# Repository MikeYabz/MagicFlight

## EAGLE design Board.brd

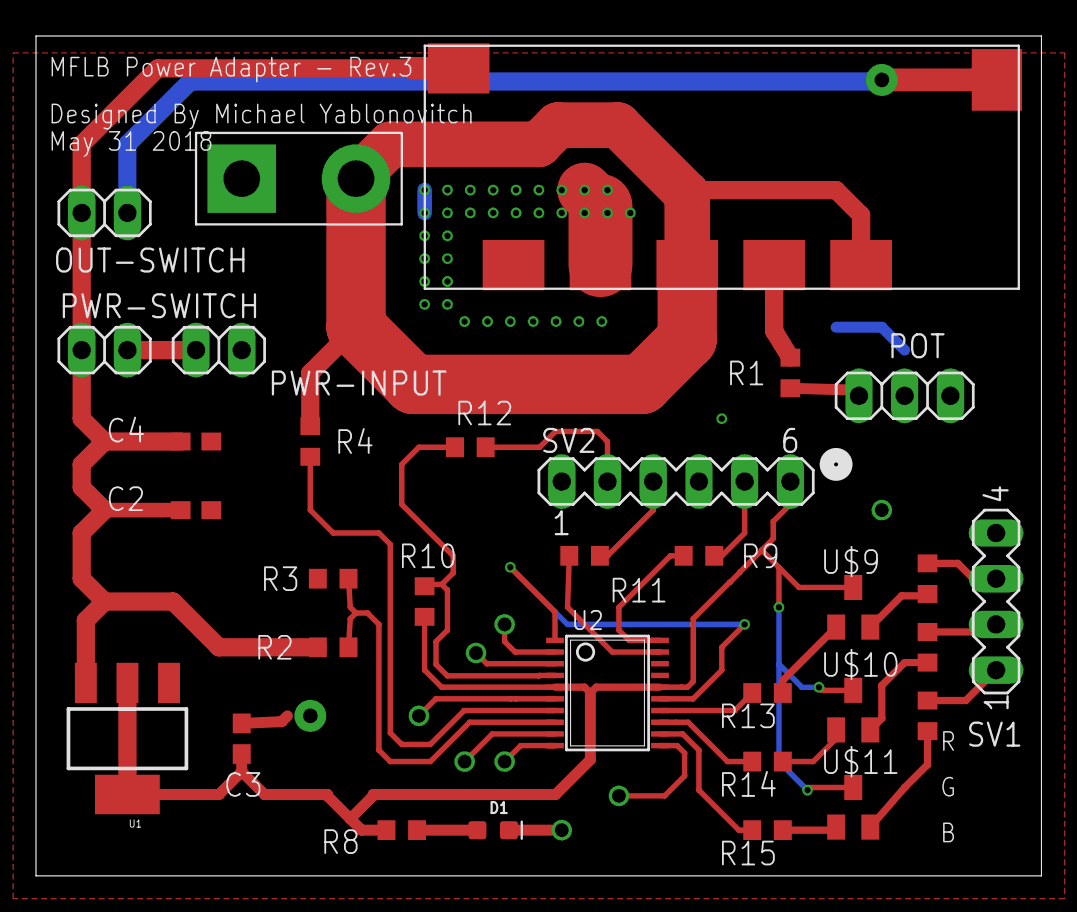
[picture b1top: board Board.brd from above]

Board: 2 copper layers, 55.9 x 46.7 mm, 32 parts (0 on the bottom side), 29 nets.

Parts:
C2: 47uF; C0603
C3: 10uF; C0603
C4: 22uF; C0603
D1: BLUE; LED-0603
OKY-T/16-D12N-C: OKY-T/16-D12N-C
OUT-SWITCH: 1X02
POT: 100k; 1X03
POWER: POWER
PWR-INPUT: 1X02
PWR-SWITCH: 1X02
R1: 9.1k; R0603
R2: 7.5k; R0603
R3: 2.5k; R0603
R4: 1k; R0603
R5, R13, R14, R15: 250; R0603
R6, R7: 200; R0603
R8: 180r; R0603
R9, R11, R12: 250r; R0603
R10: 3k3; R0603
SV1: MA04-1
SV2: MA06-1
U1: SOT223
U2: STM32F07; TSSOP20
U$9, U$10, U$11: P-MOS-FET; SOT23

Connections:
+3V3: C3.1, R8.2, R10.1, SV2.6, U1.2, U1.4, U2.5, U2.16, U$9.E, U$10.E, U$11.E
GND: C2.2, C3.2, C4.2, D1.C, OKY-T/16-D12N-C.PIN4, POT.2, POWER.GND, PWR-INPUT.1, R3.1, SV1.4, SV2.4, U1.1, U2.1, U2.15
LED-B: R15.2, U2.12
LED-G: R14.2, U2.13
LED-R: R13.2, U2.14
unnamed: OKY-T/16-D12N-C.PIN1, OUT-SWITCH.2
unnamed: R5.2, SV1.3
unnamed: POT.1, R1.1
unnamed: OKY-T/16-D12N-C.PIN6, R1.2
unnamed: R6.2, SV1.2
unnamed: R7.2, SV1.1
unnamed: R13.1, U$9.B
unnamed: R14.1, U$10.B
unnamed: R4.2, U2.7
unnamed: D1.A, R8.1
unnamed: R15.1, U$11.B
unnamed: R5.1, U$9.C
unnamed: R6.1, U$10.C
unnamed: R2.2, R3.2, U2.8
unnamed: R7.1, U$11.C
unnamed: R9.2, SV2.5
unnamed: R11.2, SV2.3
unnamed: R12.2, SV2.2
NRST: R10.2, R12.1, U2.4
SWCLK: R9.1, U2.20
SWDIO: R11.1, U2.19
VBAT: PWR-INPUT.2, PWR-SWITCH.2
VIN: C2.1, C4.1, OKY-T/16-D12N-C.PIN2, OUT-SWITCH.1, PWR-SWITCH.1, R2.1, U1.3
VOUT: OKY-T/16-D12N-C.PIN5, OKY-T/16-D12N-C.PIN7, POWER.VOUT, R4.1

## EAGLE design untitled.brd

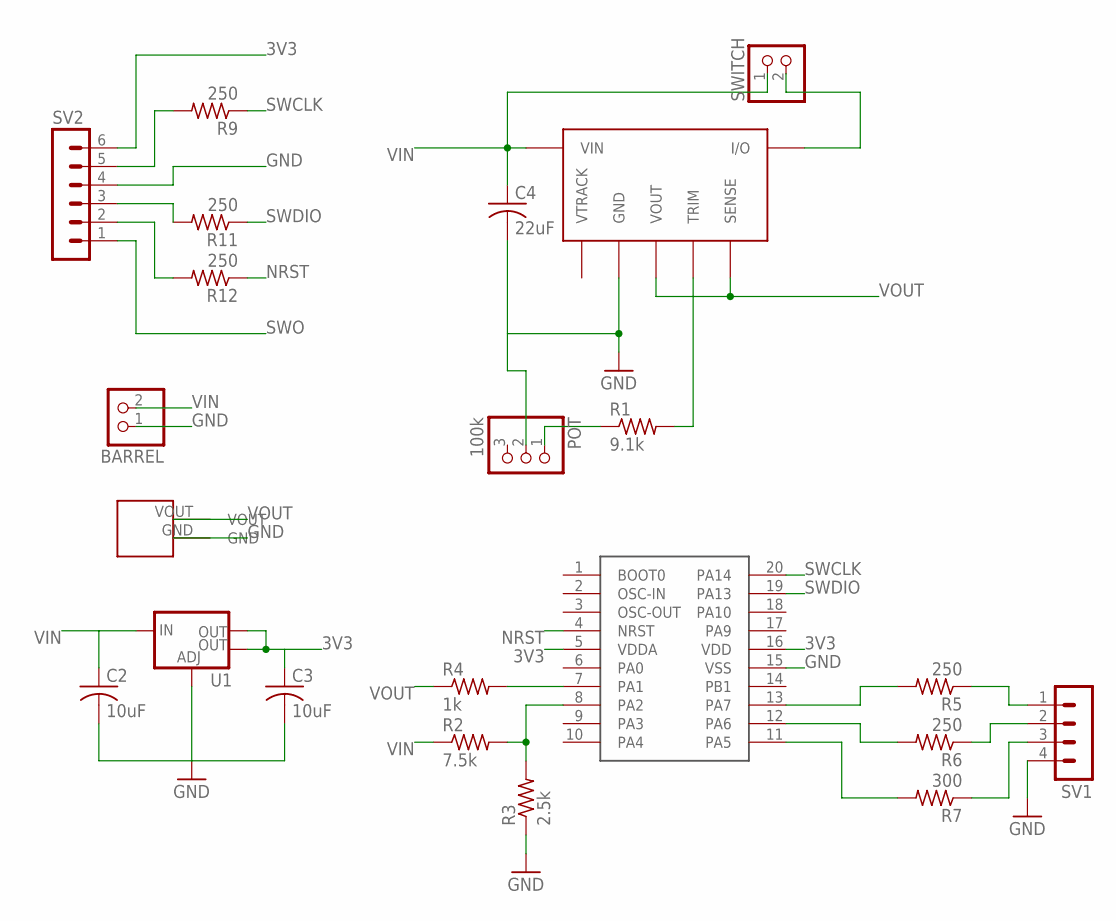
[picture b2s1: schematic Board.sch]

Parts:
BARREL: PINHD-1X2; 1X02
C2, C3: 10uF; C0805
C4: 22uF; C0805
OKY-T/16-D12N-C: OKY-T/16-D12N-C
POT: 100k; 1X03
POWER: POWER
R1: 9.1k; R0805
R2: 7.5k; R0805
R3: 2.5k; R0805
R4: 1k; R0805
R5, R6, R9, R11, R12: 250; R0805
R7: 300; R0805
SV1: MA04-1
SV2: MA06-1
SWITCH: PINHD-1X2; 1X02
U1: V_REG_LM1117SOT223; SOT223
U$1: STM32F07; TSSOP20

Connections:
3V3: C3.1, SV2.6, U1.2 (OUT), U1.4 (OUT), U$1.5 (VDDA), U$1.16 (VDD)
GND: BARREL.1, C2.2, C3.2, C4.2, OKY-T/16-D12N-C.PIN4 (GND), POT.2, POWER.GND, R3.1, SV1.4, SV2.4, U1.1 (ADJ), U$1.15 (VSS)
unnamed: OKY-T/16-D12N-C.PIN1 (I/O), SWITCH.2
unnamed: R5.1, SV1.1
unnamed: POT.1, R1.1
unnamed: OKY-T/16-D12N-C.PIN6 (TRIM), R1.2
unnamed: R2.2, R3.2, U$1.8 (PA2)
unnamed: R7.2, U$1.11 (PA5)
unnamed: R5.2, U$1.13 (PA7)
unnamed: R6.2, U$1.12 (PA6)
unnamed: R4.2, U$1.7 (PA1)
unnamed: R6.1, SV1.2
unnamed: R7.1, SV1.3
unnamed: R9.2, SV2.5
unnamed: R11.2, SV2.3
unnamed: R12.2, SV2.2
NRST: R12.1, U$1.4 (NRST)
SWCLK: R9.1, U$1.20 (PA14)
SWDIO: R11.1, U$1.19 (PA13)
SWO: SV2.1
VIN: BARREL.2, C2.1, C4.1, OKY-T/16-D12N-C.PIN2 (VIN), R2.1, SWITCH.1, U1.3 (IN)
VOUT: OKY-T/16-D12N-C.PIN5 (VOUT), OKY-T/16-D12N-C.PIN7 (SENSE), POWER.VOUT, R4.1

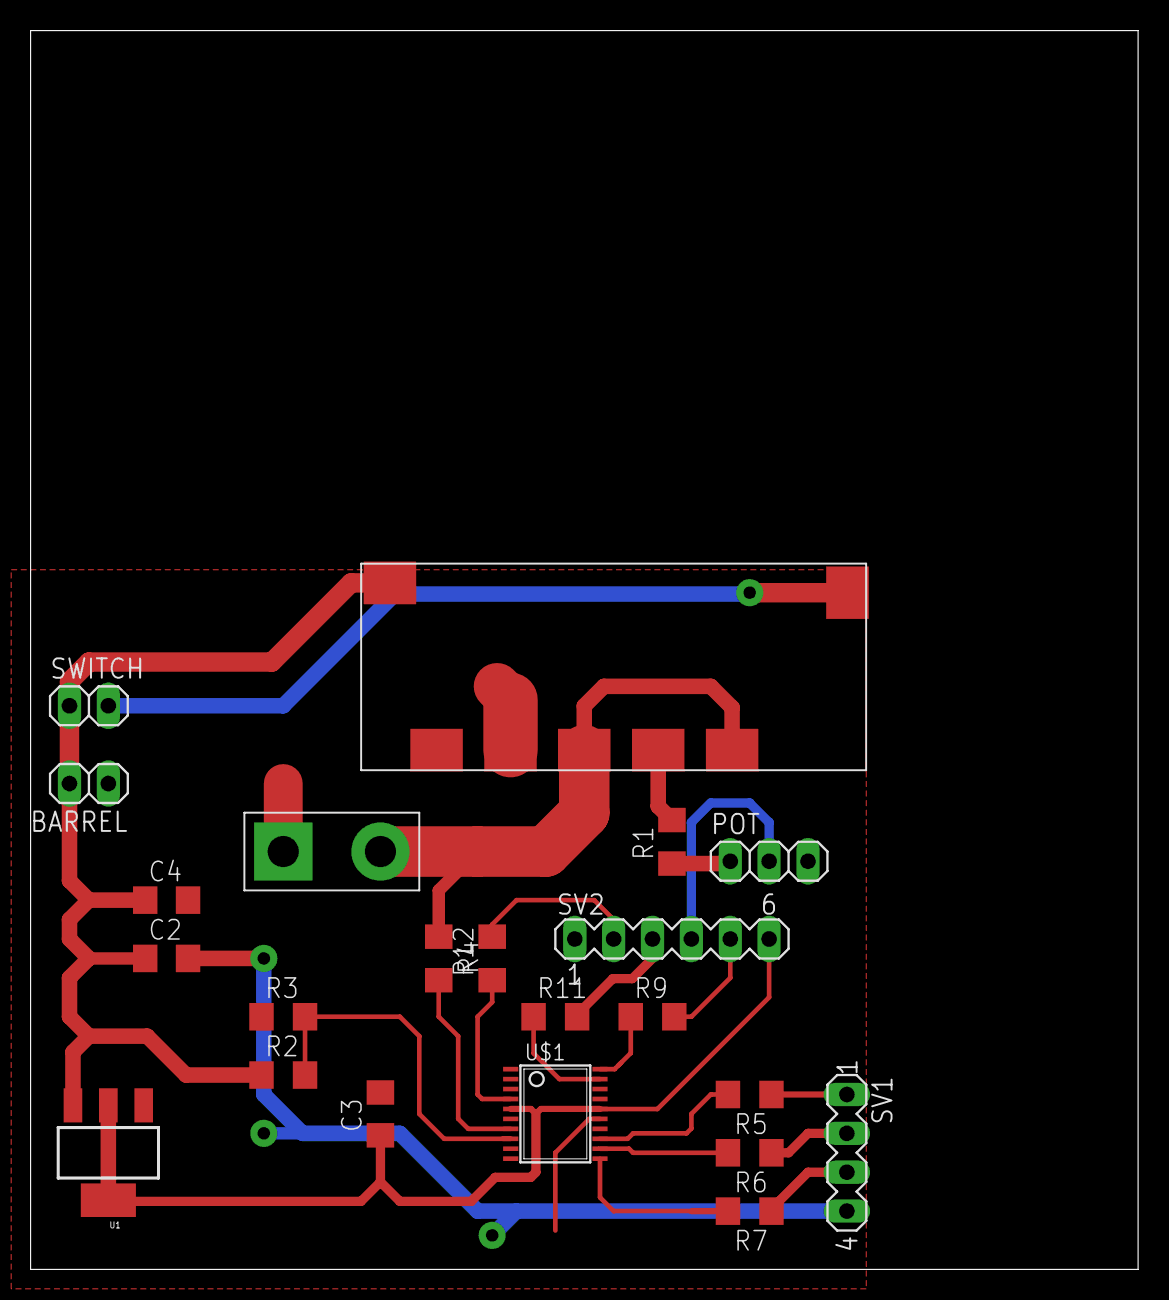
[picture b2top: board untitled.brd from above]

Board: 2 copper layers, 72.4 x 81.0 mm, 22 parts (0 on the bottom side), 21 nets.

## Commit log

2018-03-20 setup
2018-03-21 changed to stm32
2018-03-21 board design done, no DRC errors
2018-05-05 Board design Rev1
2018-05-09 preliminary rev 2
2018-05-10 rev 2 preliminary, added power LED, power switch, necessary MCU pullups/downs and fets for the RGB
2018-05-10 removed backups
2018-05-31 switched n-mos to p-mos for common cathode RGBs
2018-06-08 temperature RGB feedback and low battery implemented, not tested
2018-06-10 removed LED current limit resistors, will now be external, fixed P-MOS footprint again cuz it was right the first time.

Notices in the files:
parts and their libraries:
SparkFun-IC-Power: Licensing: Creative Commons ShareAlike 4.0 International - https://creativecommons.org/licenses/by-sa/4.0
